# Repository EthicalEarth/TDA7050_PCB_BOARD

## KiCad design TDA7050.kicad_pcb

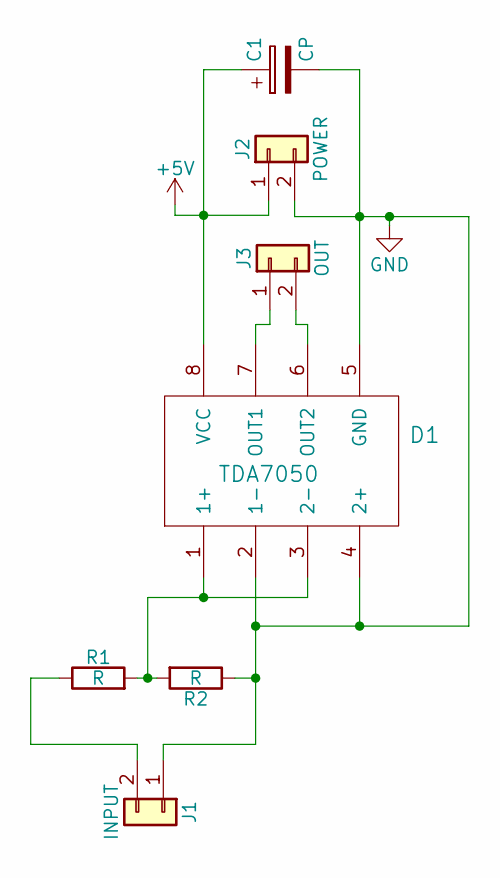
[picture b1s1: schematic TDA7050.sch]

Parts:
C1: CP; CP_Radial_D13.0mm_P7.50mm
D1: TDA7050; DIP-8_W7.62mm_LongPads
J1: INPUT; Pin_Header_Straight_1x02_Pitch2.54mm
J2: POWER; Pin_Header_Straight_1x02_Pitch2.54mm
J3: OUT; Pin_Header_Straight_1x02_Pitch2.54mm
R1, R2: R; R_Axial_DIN0309_L9.0mm_D3.2mm_P5.08mm_Vertical

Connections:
+5V: C1.1, D1.8 (VCC), J2.1
GND: C1.2, D1.2 (1-), D1.4 (2+), D1.5 (GND), J1.1, J2.2, R2.1
unnamed: D1.1 (1+), D1.3 (2-), R1.2, R2.2
unnamed: D1.6 (OUT2), J3.2
unnamed: D1.7 (OUT1), J3.1
unnamed: J1.2, R1.1

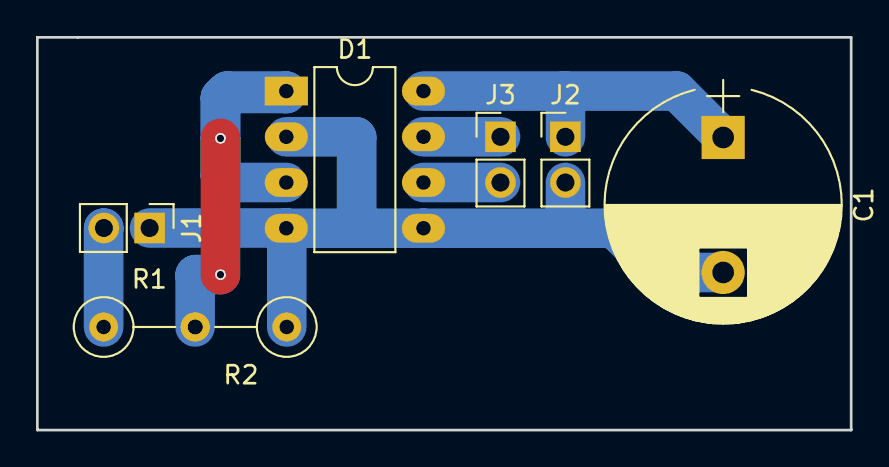
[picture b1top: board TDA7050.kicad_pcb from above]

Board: 2 copper layers, 45.2 x 21.8 mm, 7 parts (0 on the bottom side), 6 nets.

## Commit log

2018-07-28 Init
2018-07-28 Message
